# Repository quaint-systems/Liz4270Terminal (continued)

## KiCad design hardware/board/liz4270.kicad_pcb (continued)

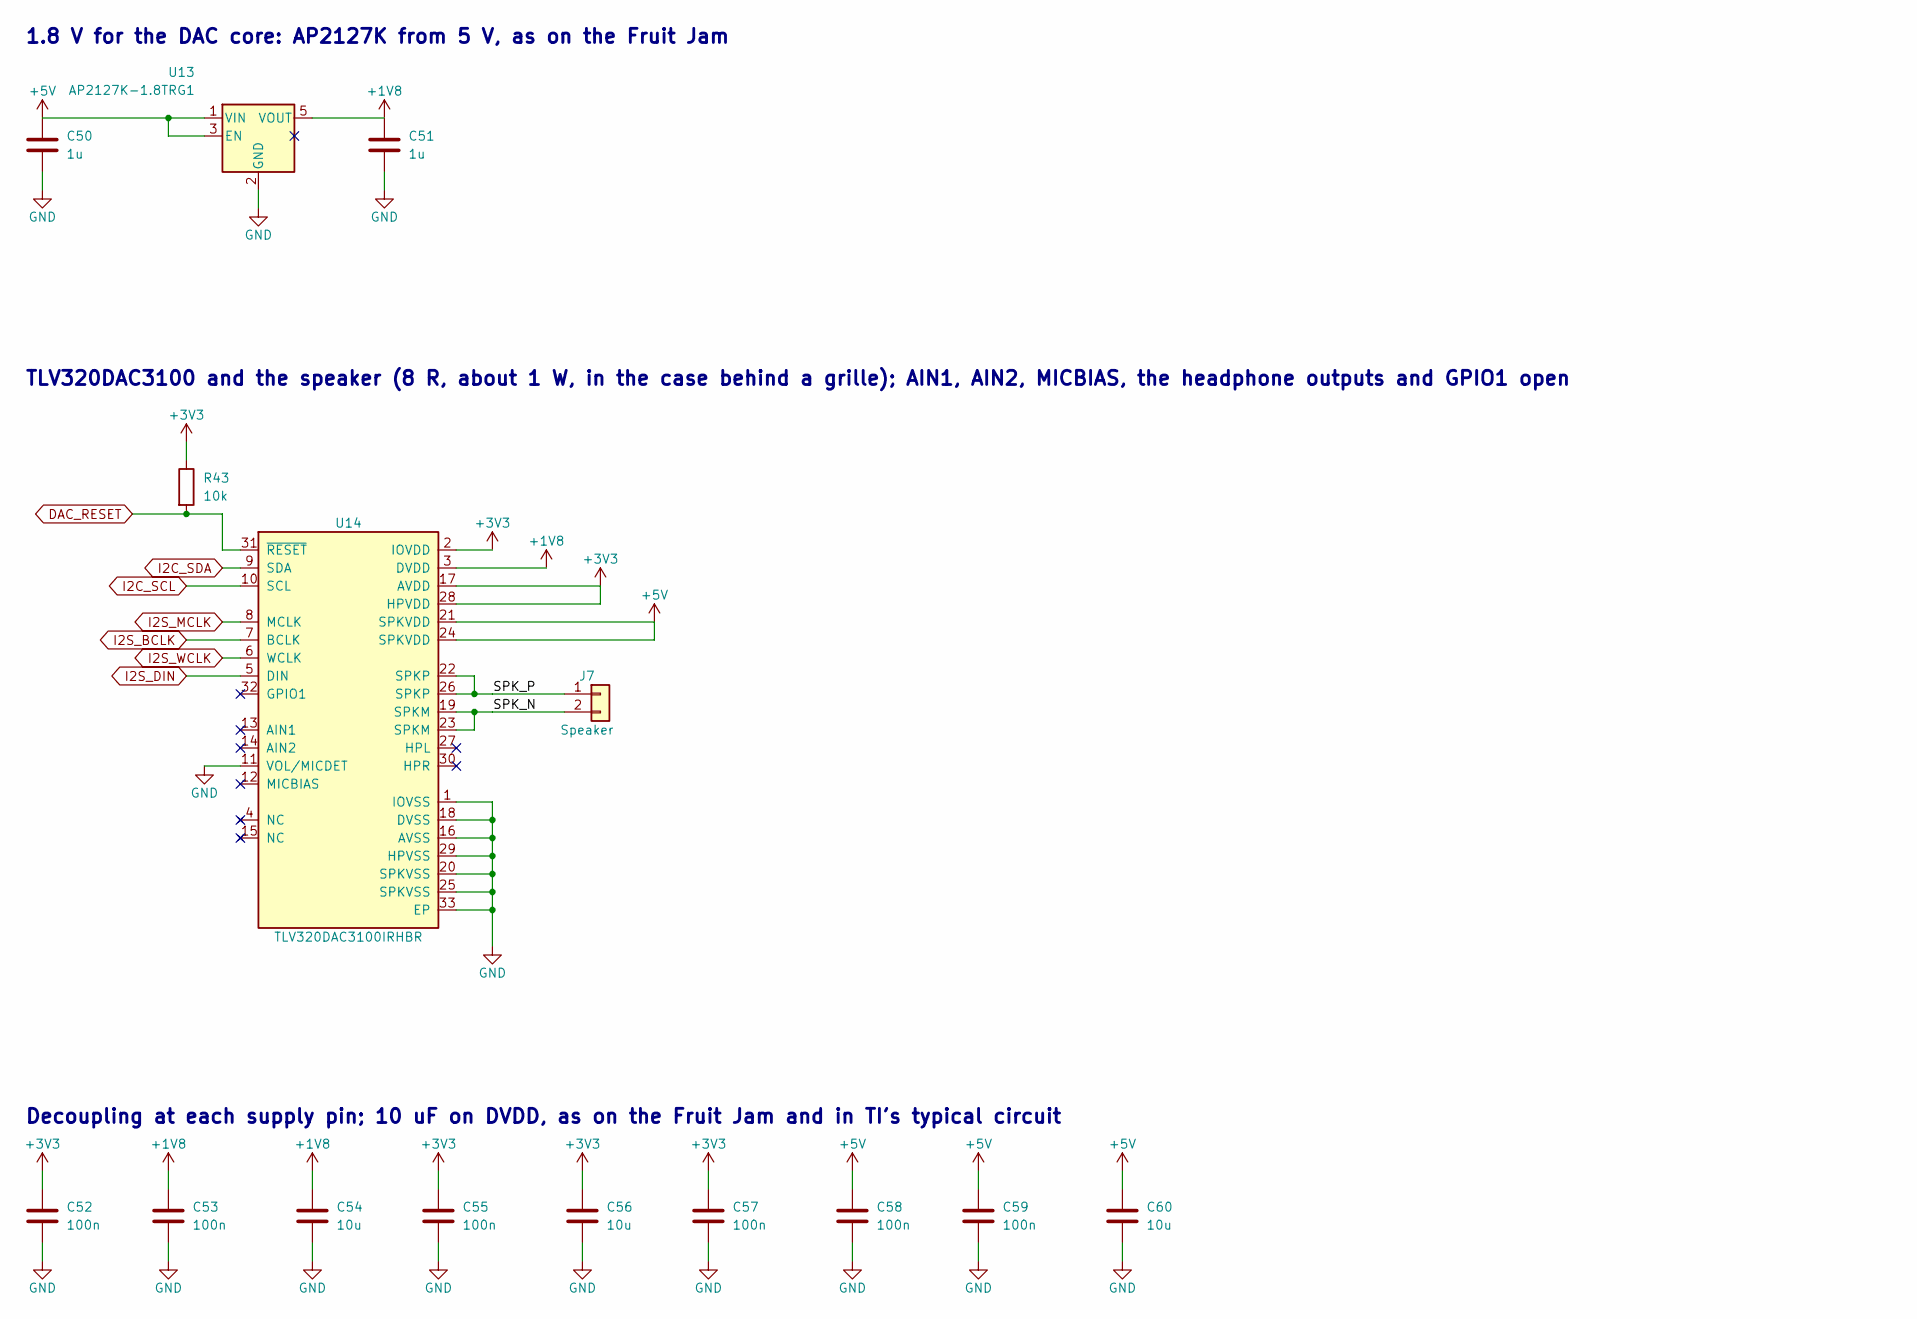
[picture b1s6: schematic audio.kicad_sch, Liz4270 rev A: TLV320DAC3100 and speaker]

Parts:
C50, C51: 1u; C_0603_1608Metric; LCSC C15849
C52, C53, C55, C57, C58, C59: 100n; C_0603_1608Metric; LCSC C14663
C54, C56, C60: 10u; C_0805_2012Metric; LCSC C15850
J7: Speaker; JST_PH_B2B-PH-K_1x02_P2.00mm_Vertical; MPN B2B-PH-K-S(LF)(SN); LCSC C131337
R43: 10k; R_0603_1608Metric; LCSC C25804
U13: AP2127K-1.8TRG1; SOT-23-5; MPN AP2127K-1.8TRG1; LCSC C151375
U14: TLV320DAC3100IRHBR; QFN-32-1EP_5x5mm_P0.5mm_EP3.45x3.45mm_ThermalVias; MPN TLV320DAC3100IRHBR; LCSC C179677

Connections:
+1V8: C51.1, C53.1, C54.1, U13.5 (VOUT), U14.3 (DVDD); also elsewhere on the board
+3V3: C52.1, C55.1, C56.1, C57.1, R43.1, U14.2 (IOVDD), U14.17 (AVDD), U14.28 (HPVDD); also elsewhere on the board
+5V: C50.1, C58.1, C59.1, C60.1, U13.1 (VIN), U13.3 (EN), U14.21 (SPKVDD), U14.24 (SPKVDD); also elsewhere on the board
/Audio/SPK_N: J7.2, U14.19 (SPKM), U14.23 (SPKM)
/Audio/SPK_P: J7.1, U14.22 (SPKP), U14.26 (SPKP)
DAC_RESET: R43.2, U14.31 (~RESET); also elsewhere on the board
GND: C50.2, C51.2, C52.2, C53.2, C54.2, C55.2, C56.2, C57.2, C58.2, C59.2, C60.2, U13.2 (GND), U14.1 (IOVSS), U14.11 (VOL/MICDET), U14.16 (AVSS), U14.18 (DVSS), U14.20 (SPKVSS), U14.25 (SPKVSS), U14.29 (HPVSS), U14.33 (EP); also elsewhere on the board
I2C_SCL: U14.10 (SCL); also elsewhere on the board
I2C_SDA: U14.9 (SDA); also elsewhere on the board
I2S_BCLK: U14.7 (BCLK); also elsewhere on the board
I2S_DIN: U14.5 (DIN); also elsewhere on the board
I2S_MCLK: U14.8 (MCLK); also elsewhere on the board
I2S_WCLK: U14.6 (WCLK); also elsewhere on the board

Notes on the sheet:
1.8 V for the DAC core: AP2127K from 5 V, as on the Fruit Jam
TLV320DAC3100 and the speaker (8 R, about 1 W, in the case behind a grille); AIN1, AIN2, MICBIAS, the headphone outputs and GPIO1 open
Decoupling at each supply pin; 10 uF on DVDD, as on the Fruit Jam and in TI's typical circuit

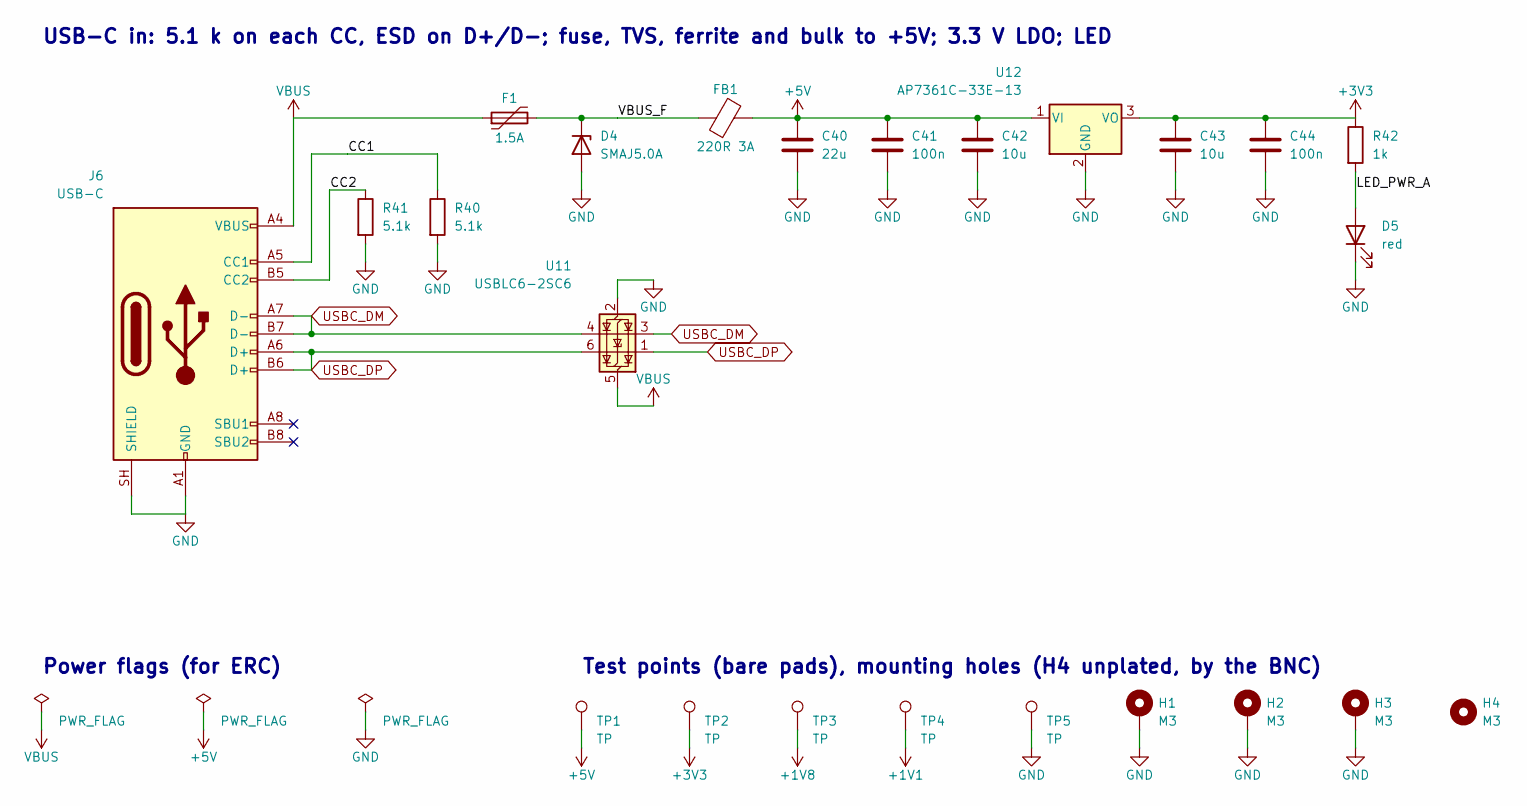
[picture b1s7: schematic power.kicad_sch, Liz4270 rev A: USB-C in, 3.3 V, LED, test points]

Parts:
C40: 22u; C_0805_2012Metric; LCSC C45783
C41, C44: 100n; C_0603_1608Metric; LCSC C14663
C42, C43: 10u; C_0805_2012Metric; LCSC C15850
D4: SMAJ5.0A; D_SMA; MPN SMAJ5.0A; LCSC C113952
D5: red; LED_0603_1608Metric; MPN KT-0603R; LCSC C2286
F1: 1.5A; Fuse_1812_4532Metric; MPN MF-MSMF150-2; LCSC C89648
FB1: 220R 3A; L_0805_2012Metric; MPN MPZ2012S221AT000; LCSC C76818
H1, H2, H3: M3; MountingHole_3.2mm_M3_Pad_Via
H4: M3; MountingHole_3.2mm_M3
J6: USB-C; USB_C_Receptacle_HRO_TYPE-C-31-M-12; MPN TYPE-C-31-M-12; LCSC C165948
R40, R41: 5.1k; R_0603_1608Metric; LCSC C23186
R42: 1k; R_0603_1608Metric; LCSC C21190
TP1, TP2, TP3, TP4, TP5: TP; TestPoint_Pad_D1.5mm
U11: USBLC6-2SC6; SOT-23-6; MPN USBLC6-2SC6; LCSC C7519
U12: AP7361C-33E-13; SOT-223-3_TabPin2; MPN AP7361C-33E-13; LCSC C500795

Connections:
+1V1: TP4.1; also elsewhere on the board
+1V8: TP3.1; also elsewhere on the board
+3V3: C43.1, C44.1, R42.1, TP2.1, U12.3 (VO); also elsewhere on the board
+5V: C40.1, C41.1, C42.1, FB1.2, TP1.1, U12.1 (VI); also elsewhere on the board
/Power/CC1: J6.A5 (CC1), R40.1
/Power/CC2: J6.B5 (CC2), R41.1
/Power/LED_PWR_A: D5.2 (A), R42.2
/Power/VBUS_F: D4.1 (K), F1.2, FB1.1
GND: C40.2, C41.2, C42.2, C43.2, C44.2, D4.2 (A), D5.1 (K), H1.1, H2.1, H3.1, J6.A1 (GND), J6.A12 (GND), J6.B1 (GND), J6.B12 (GND), J6.SH (SHIELD), R40.2, R41.2, TP5.1, U11.2 (GND), U12.2 (GND); also elsewhere on the board
USBC_DM: J6.A7 (D-), J6.B7 (D-), U11.3 (I/O2), U11.4 (I/O2); also elsewhere on the board
USBC_DP: J6.A6 (D+), J6.B6 (D+), U11.1 (I/O1), U11.6 (I/O1); also elsewhere on the board
VBUS: F1.1, J6.A4 (VBUS), J6.A9 (VBUS), J6.B4 (VBUS), J6.B9 (VBUS), U11.5 (VBUS)

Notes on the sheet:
USB-C in: 5.1 k on each CC, ESD on D+/D-; fuse, TVS, ferrite and bulk to +5V; 3.3 V LDO; LED
Power flags (for ERC)
Test points (bare pads), mounting holes (H4 unplated, by the BNC)

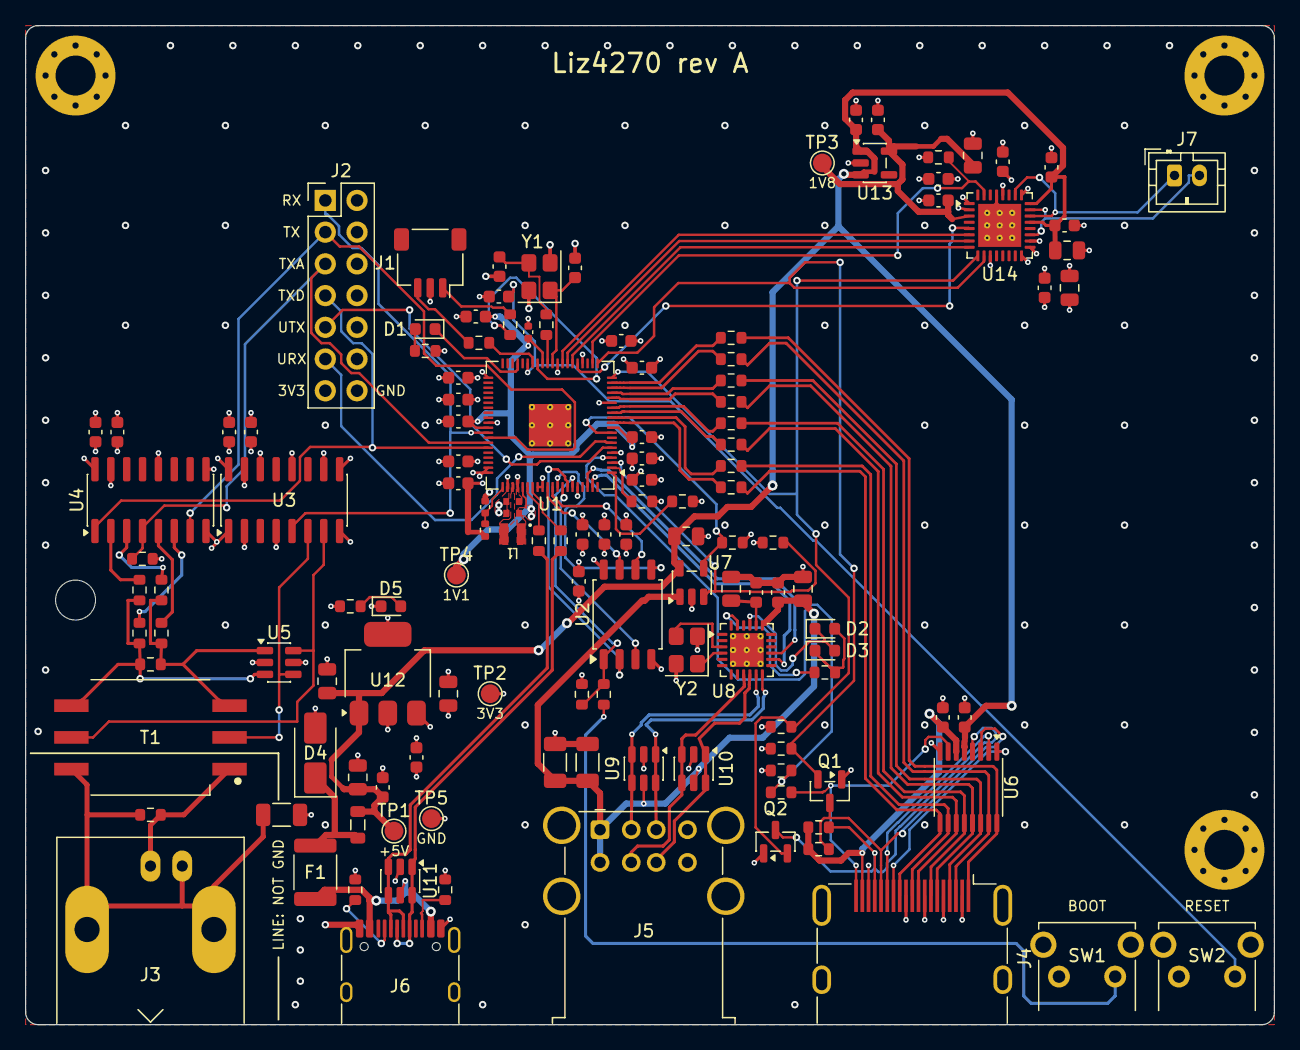
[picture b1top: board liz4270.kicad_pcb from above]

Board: 4 copper layers, 100.0 x 80.0 mm, 136 parts (0 on the bottom side), 98 nets.

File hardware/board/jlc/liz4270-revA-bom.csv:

Comment,Designator,Footprint,LCSC Part #
4.7u,"C1,C2,C3,C4",RPi_C_1005_Wide,C23733
100n,"C5,C6,C7,C8,C9,C10,C11,C12,C13,C14,C15,C16,C17,C18,C21,C22,C24,C30,C31,C36,C41,C44,C52,C53,C55,C57,C58,C59",C_0603_1608Metric,C14663
15p,"C19,C20",C_0603_1608Metric,C1644
10n,"C23,C25",C_0603_1608Metric,C57112
10u,"C32,C33,C35,C42,C43,C54,C56,C60",C_0805_2012Metric,C15850
1u,"C34,C50,C51",C_0603_1608Metric,C15849
100u,"C37,C38",C_1206_3216Metric,C15008
22u,C40,C_0805_2012Metric,C45783
red,"D1,D2,D3,D5",LED_0603_1608Metric,C2286
SMAJ5.0A,D4,D_SMA,C113952
1.5A,F1,Fuse_1812_4532Metric,C89648
220R 3A,FB1,L_0805_2012Metric,C76818
SWD,J1,JST_SH_SM03B-SRSS-TB_1x03-1MP_P1.00mm_Horizontal,C2763613
BNC,J3,BNC_Amphenol_B6252HB-NPP3G-50_Horizontal,C22457552
HDMI,J4,HDMI_A_Molex_208658-1001_Horizontal,C916313
USB-A x2,J5,USB_A_Wuerth_61400826021_Horizontal_Stacked,C588409
USB-C,J6,USB_C_Receptacle_HRO_TYPE-C-31-M-12,C165948
Speaker,J7,JST_PH_B2B-PH-K_1x02_P2.00mm_Vertical,C131337
3.3u,L1,Abracon_AOTA-B201610S3R3-101-T,C42411119
BSS138,"Q1,Q2",SOT-23,C82045
33,R1,R_0402_1005Metric,C25105
1k,"R2,R4,R9,R42",R_0603_1608Metric,C21190
27,"R5,R6",R_0603_1608Metric,C25190
4.7k,"R7,R8,R16,R33,R34",R_0603_1608Metric,C23162
120,R10,R_0603_1608Metric,C22787
150,"R11,R12",R_0603_1608Metric,C22808
33,"R13,R14",R_0603_1608Metric,C23140
510,R15,R_0603_1608Metric,C23193
220,"R20,R21,R22,R23,R24,R25,R26,R27,R32",R_0603_1608Metric,C22962
10k,"R28,R29,R35,R43",R_0603_1608Metric,C25804
2k,"R30,R31",R_0603_1608Metric,C22975
5.1k,"R36,R40,R41",R_0603_1608Metric,C23186
100,"R44,R45",R_0603_1608Metric,C22775
BOOTSEL,"SW1,SW2",SW_CK_PTS645V_Angled,C285519
RP2350B,U1,QFN-80-1EP_10x10mm_P0.4mm_EP3.4x3.4mm_ThermalVias,C42415655
W25Q128JVSIQ,U2,SOIC-8_5.3x5.3mm_P1.27mm,C97521
DS34LV86TMX/NOPB,U3,SOIC-16_3.9x9.9mm_P1.27mm,C140249
DS34LV87TM/NOPB,U4,SOIC-16_3.9x9.9mm_P1.27mm,C1543778
TPD13S523PWR,U6,TSSOP-16_4.4x5mm_P0.65mm,C2865622
AP2171WG-7,U7,SOT-23-5,C110466
CH334F,U8,QFN-24-1EP_4x4mm_P0.5mm_EP2.7x2.7mm_ThermalVias,C5187527
USBLC6-2SC6,"U9,U10,U11",SOT-23-6,C7519
AP7361C-33E-13,U12,SOT-223-3_TabPin2,C500795
AP2127K-1.8TRG1,U13,SOT-23-5,C151375
TLV320DAC3100IRHBR,U14,QFN-32-1EP_5x5mm_P0.5mm_EP3.45x3.45mm_ThermalVias,C179677
12MHz,"Y1,Y2",Crystal_SMD_3225-4Pin_3.2x2.5mm,C20625731

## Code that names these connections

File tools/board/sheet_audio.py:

# Copyright (c) 2026, CoffeeMuse
# SPDX-License-Identifier: ISC

"""The audio sheet: the TLV320DAC3100's beep generator as #18 drives it (I2C0 at 0x18, MCLK on GPIO25, the DAC
the I2S master), speaker only (spec, "Sound"). DVDD is 1.8 V: its absolute maximum is 2.5 V (TI SLAS671C, 4.1).

Two small circuits are drawn. The 1.8 V regulator runs left to right from +5V to +1V8, EN tied to VIN. The DAC
takes its controls and clocks from the left, its reset pulled up there; on the right each supply pin steps out to
an upright rail symbol, the grounds share one wire, and each speaker output's two pins join on their way to J7."""

import parts as P


def build(project):
    s = project.sheet('audio.kicad_sch', 'Audio', 'TLV320DAC3100 and speaker')

    # TI's power-up order (SLAS671C, 6.3.1) is SPKVDD, IOVDD, DVDD, then AVDD and HPVDD. IOVDD shares 3.3 V with AVDD and
    # HPVDD, so no 1.8 V source meets it; TI calls the part tolerant of order (section 8), and the firmware resets it.
    d = s.drawing('1.8 V for the DAC core: AP2127K from 5 V, as on the Fruit Jam')
    d.add(P.AP2127K_18, 'U13', {'VIN': '+5V', 'GND': 'GND', 'EN': '+5V', 'VOUT': '+1V8'}, nc=['NC'], at=(0, 0))
    d.add(P.C1U, 'C50', {'1': '+5V', '2': 'GND'}, at=(-30.48, 1.27))       # clear of U13's part number
    d.add(P.C1U, 'C51', {'1': '+1V8', '2': 'GND'}, at=(17.78, 1.27))
    d.wire('U13.1', 'C50.1')
    d.wire('U13.3', (-12.7, 0), (-12.7, -2.54))
    d.label('+5V', (-30.48, -2.54), 'up')
    d.wire('U13.5', 'C51.1')
    d.label('+1V8', (17.78, -2.54), 'up')

    # AIN1 and AIN2 are left open: the DAC can bias them (page 1, register 50), so TI's engineers advise against
    # grounding them, and the firmware never routes them. VOL/MICDET is grounded; both its functions are off at reset.
    d = s.drawing('TLV320DAC3100 and the speaker (8 R, about 1 W, in the case behind a grille); AIN1, AIN2, MICBIAS, '
                  'the headphone outputs and GPIO1 open')
    d.add(P.TLV320DAC3100, 'U14', {
        'IOVSS': 'GND', 'IOVDD': '+3V3', 'DVDD': '+1V8', 'DIN': 'I2S_DIN', 'WCLK': 'I2S_WCLK', 'BCLK': 'I2S_BCLK',
        'MCLK': 'I2S_MCLK', 'SDA': 'I2C_SDA', 'SCL': 'I2C_SCL', 'VOL/MICDET': 'GND',
        'AVSS': 'GND', 'AVDD': '+3V3', 'DVSS': 'GND', 'SPKM': 'SPK_N', 'SPKVSS': 'GND', 'SPKVDD': '+5V',
        'SPKP': 'SPK_P', 'HPVDD': '+3V3', 'HPVSS': 'GND', '~{RESET}': 'DAC_RESET', 'EP': 'GND'},
        nc=['NC', 'AIN1', 'AIN2', 'MICBIAS', 'HPL', 'HPR', 'GPIO1'], at=(0, 0))

    # Reset, held by R43 until the firmware drives GPIO22
    d.add(P.R10K, 'R43', {'1': '+3V3', '2': 'DAC_RESET'}, at=(-22.86, -34.29))
    d.wire('U14.31', (-17.78, -25.4), (-17.78, -30.48), 'R43.2', (-30.48, -30.48))
    d.label('DAC_RESET', (-30.48, -30.48), 'left')
    d.wire('U14.11', (-20.32, 5.08))
    d.label('GND', (-20.32, 5.08), 'down')

    # Supplies, each a step further right so that its symbol stands clear of the wires above: IOVDD, DVDD, AVDD with
    # HPVDD, then both SPKVDD
    d.wire('U14.2', (20.32, -25.4))
    d.label('+3V3', (20.32, -25.4), 'up')
    d.wire('U14.3', (27.94, -22.86))
    d.label('+1V8', (27.94, -22.86), 'up')
    d.wire('U14.17', (35.56, -20.32))
    d.wire('U14.28', (35.56, -17.78), (35.56, -20.32))
    d.label('+3V3', (35.56, -20.32), 'up')
    d.wire('U14.21', (43.18, -15.24))
    d.wire('U14.24', (43.18, -12.7), (43.18, -15.24))
    d.label('+5V', (43.18, -15.24), 'up')

    # The speaker: each output is two pins, joined on the way to J7
    d.add(P.JST_PH2, 'J7', {'1': 'SPK_P', '2': 'SPK_N'}, at=(35.56, -5.08))
    d.wire('U14.26', 'J7.1')
    d.wire('U14.22', (17.78, -7.62), (17.78, -5.08))
    d.wire('U14.19', 'J7.2')
    d.wire('U14.23', (17.78, 0), (17.78, -2.54))
    d.label('SPK_P', (20.32, -5.08), 'right')
    d.label('SPK_N', (20.32, -2.54), 'right')

    # The grounds, joined
    d.wire('U14.1', (20.32, 10.16), (20.32, 30.48))
    for (pin, y) in (('18', 12.7), ('16', 15.24), ('29', 17.78), ('20', 20.32), ('25', 22.86), ('33', 25.4)):
        d.wire(f'U14.{pin}', (20.32, y))
    d.label('GND', (20.32, 30.48), 'down')

    g = s.group('Decoupling at each supply pin; 10 uF on DVDD, as on the Fruit Jam and in TI\'s typical circuit')
    for (ref, spec, net) in (('C52', P.C100N, '+3V3'), ('C53', P.C100N, '+1V8'), ('C54', P.C10U, '+1V8'),
                             ('C55', P.C100N, '+3V3'), ('C56', P.C10U, '+3V3'), ('C57', P.C100N, '+3V3'),
                             ('C58', P.C100N, '+5V'), ('C59', P.C100N, '+5V'), ('C60', P.C10U, '+5V')):
        g.add(spec, ref, {'1': net, '2': 'GND'})

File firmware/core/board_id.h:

// Copyright (c) 2026, CoffeeMuse
// SPDX-License-Identifier: ISC

// Which board the firmware runs on (#97). One UF2 serves the Fruit Jam and
// the Liz4270 board, so at power-on the firmware reads GPIO 4 and 5 with the
// pads' pull-ups on. The Fruit Jam's buttons 2 and 3 are bare switches to
// ground there, so it reads both high. Revision A holds both low through
// 4.7 kOhm (the unified board spec, "Pin map"). Either one low alone is
// unknown: on a Fruit Jam, a button held through reset. A later revision can
// claim one. The ID is written in pin order, GPIO4 first: `11`, `00`.
//
// Which boards have the signals revision A added is decided here too, not by
// the drivers that read them: only revision A has the USB fault flag on GPIO6
// and hot-plug detect on GPIO7. On the Fruit Jam those are bare header pins,
// so nothing reads them.

#ifndef LIZ_BOARD_ID_H
#define LIZ_BOARD_ID_H

#include <stdbool.h>

typedef enum {
    BOARD_UNKNOWN = 0,
    BOARD_FRUIT_JAM = 1,
    BOARD_REV_A = 2,
} board_t;

// GPIO 4 and 5 as read with the pull-ups on.
board_t board_from_id(bool gpio4, bool gpio5);

// "Fruit Jam", "Liz4270 rev A" or "unknown".
const char *board_name(board_t board);

// The USB-A load switch's fault flag on GPIO6 (usb_fault.h).
bool board_has_usb_fault(board_t board);

// HDMI hot-plug detect on GPIO7.
bool board_has_hpd(board_t board);

#endif
